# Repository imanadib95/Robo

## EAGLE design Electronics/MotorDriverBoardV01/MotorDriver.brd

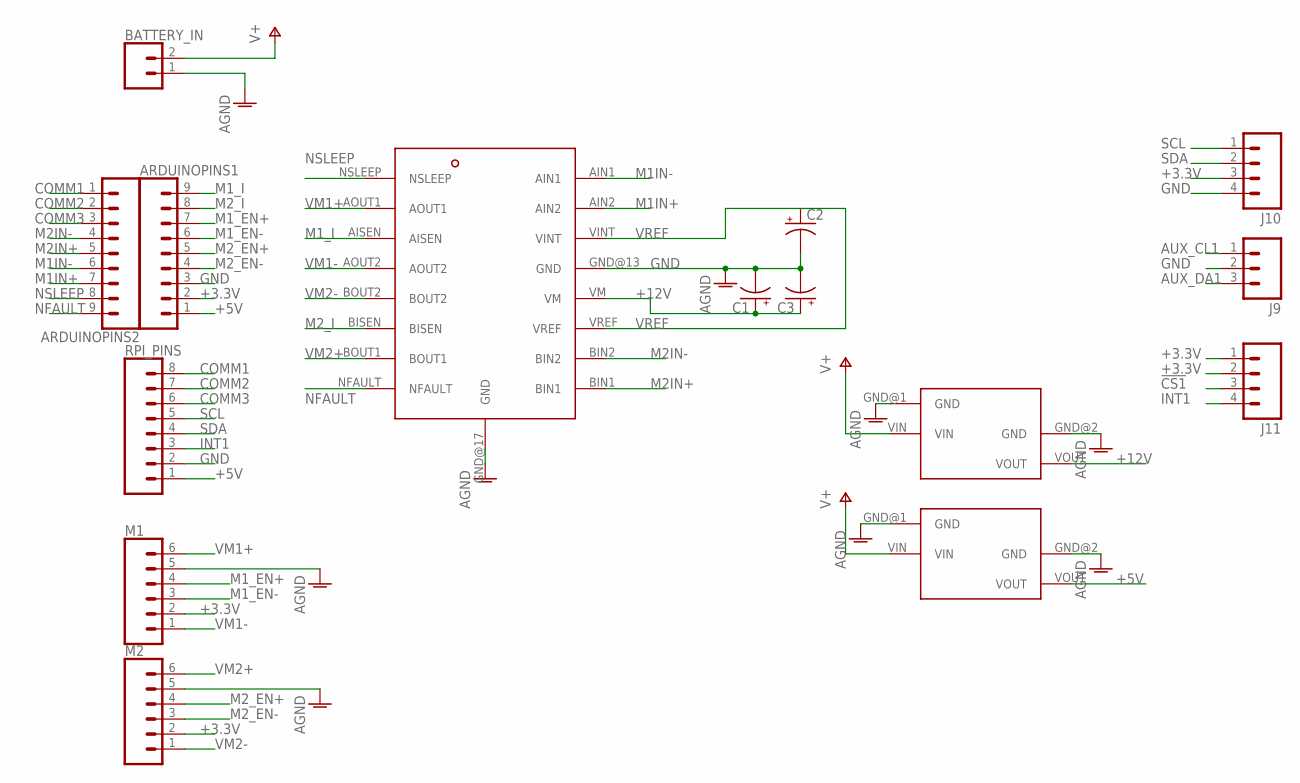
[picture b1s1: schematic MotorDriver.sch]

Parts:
ARDUINOPINS1, ARDUINOPINS2: CONN_09; 1X09
BATTERY_IN: CONN_02; 1X02
C1, C2, C3: CPOL-USTT2D5; TT2D5
HBRIDGE: DRV8848
J9: M03PTH; 1X03
J10, J11: M04PTH; 1X04
M1, M2: CONN_06SILK_FEMALE_PTH; 1X06
RPI_PINS: CONN_08"; 1X08
VREG_5V, VREG_12V: U3V50F12

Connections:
!CS1: J11.3
+3.3V: ARDUINOPINS1.2, J10.3, J11.1, J11.2, M1.2, M2.2
+5V: ARDUINOPINS1.1, RPI_PINS.1, VREG_5V.VOUT
+12V: C1.+, C3.+, HBRIDGE.VM, VREG_12V.VOUT
AUX_CL1: J9.1
AUX_DA1: J9.3
COMM1: ARDUINOPINS2.1, RPI_PINS.8
COMM2: ARDUINOPINS2.2, RPI_PINS.7
COMM3: ARDUINOPINS2.3, RPI_PINS.6
GND: ARDUINOPINS1.3, BATTERY_IN.1, C1.-, C2.-, C3.-, HBRIDGE.GND@13 (GND), HBRIDGE.GND@17 (GND), J9.2, J10.4, M1.5, M2.5, RPI_PINS.2, VREG_5V.GND@1 (GND), VREG_5V.GND@2 (GND), VREG_12V.GND@1 (GND), VREG_12V.GND@2 (GND)
INT1: J11.4, RPI_PINS.3
M1IN+: ARDUINOPINS2.7, HBRIDGE.AIN2
M1IN-: ARDUINOPINS2.6, HBRIDGE.AIN1
M1_EN+: ARDUINOPINS1.7, M1.4
M1_EN-: ARDUINOPINS1.6, M1.3
M1_I: ARDUINOPINS1.9, HBRIDGE.AISEN
M2IN+: ARDUINOPINS2.5, HBRIDGE.BIN1
M2IN-: ARDUINOPINS2.4, HBRIDGE.BIN2
M2_EN+: ARDUINOPINS1.5, M2.4
M2_EN-: ARDUINOPINS1.4, M2.3
M2_I: ARDUINOPINS1.8, HBRIDGE.BISEN
NFAULT: ARDUINOPINS2.9, HBRIDGE.NFAULT
NSLEEP: ARDUINOPINS2.8, HBRIDGE.NSLEEP
SCL: J10.1, RPI_PINS.5
SDA: J10.2, RPI_PINS.4
V+: BATTERY_IN.2, VREG_5V.VIN, VREG_12V.VIN
VM1+: HBRIDGE.AOUT1, M1.6
VM1-: HBRIDGE.AOUT2, M1.1
VM2+: HBRIDGE.BOUT1, M2.6
VM2-: HBRIDGE.BOUT2, M2.1
VREF: C2.+, HBRIDGE.VINT, HBRIDGE.VREF

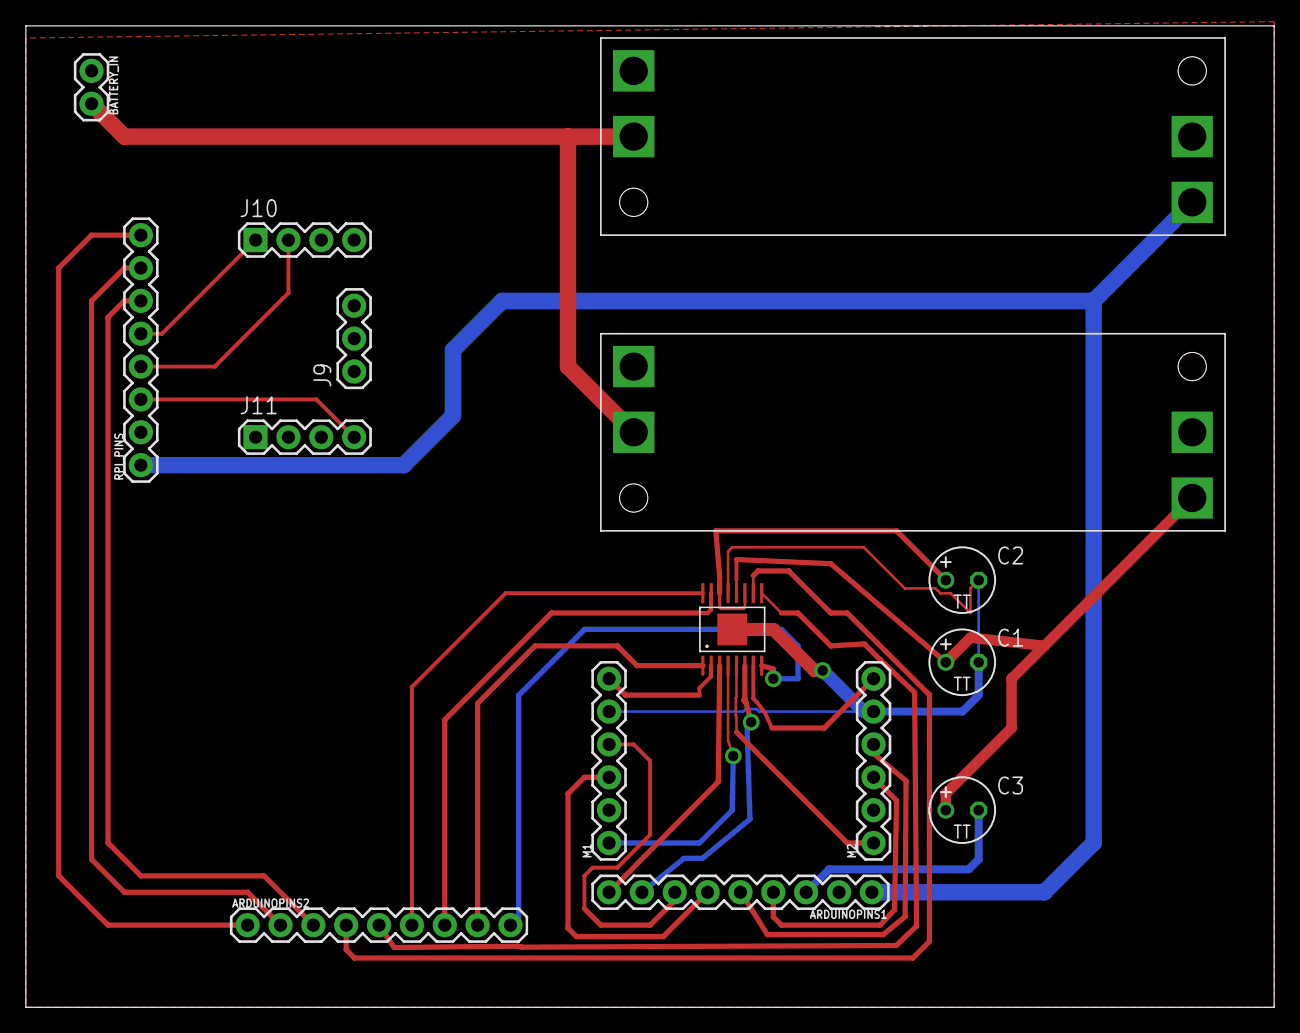
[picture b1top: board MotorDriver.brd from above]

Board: 2 copper layers, 96.5 x 75.9 mm, 15 parts (0 on the bottom side), 28 nets.

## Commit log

2018-08-24 Solidworks Files V01 and V02
2018-08-25 Driver Board V01 Finished

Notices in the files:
parts and their libraries:
SparkFun-Connectors: Licensing: Creative Commons ShareAlike 4.0 International - https://creativecommons.org/licenses/by-sa/4.0
